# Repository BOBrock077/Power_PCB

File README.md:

# MAX1954 Buck Converter Practice

Personal power supply design practice using MAX1954 synchronous buck controller.

Main goals:
- Practice synchronous buck converter design
- Learn power stage PCB layout
- Evaluate DH/LX switching behavior
- Test snubber effectiveness
- Observe switching noise and ringing

---

## Current Status

- [x] Schematic
- [ ] PCB layout
- [ ] ERC/DRC cleanup
- [ ] Prototype
- [ ] Oscilloscope validation

---

## Basic Specs

| Item | Value |
|---|---|
| VIN | 12V |
| VOUT | TBD |
| Controller | MAX1954 |
| MOSFET | FDS6690A |
| Topology | Synchronous Buck |

---

## Things To Learn

- Bootstrap circuit behavior
- DH/LX waveform
- MOSFET switching loss
- Snubber tuning
- Ground return path
- Switching loop minimization

---

## Notes

### Snubber

Current value:
- 1500pF capacitor
- resistor TBD

Need waveform validation later.

---

## TODO

- [ ] Add input bulk capacitor
- [ ] Check compensation network
- [ ] Measure LX ringing
- [ ] Optimize MOSFET placement
- [ ] Thermal estimation

---

## Git Commit Style

```bash
PCB: move MOSFET closer to controller
SCH: update bootstrap capacitor
TEST: measure LX overshoot
```

---

## References

- MAX1954 Datasheet
- TI Power Layout Guidelines
- Analog Devices Buck Converter Layout Notes

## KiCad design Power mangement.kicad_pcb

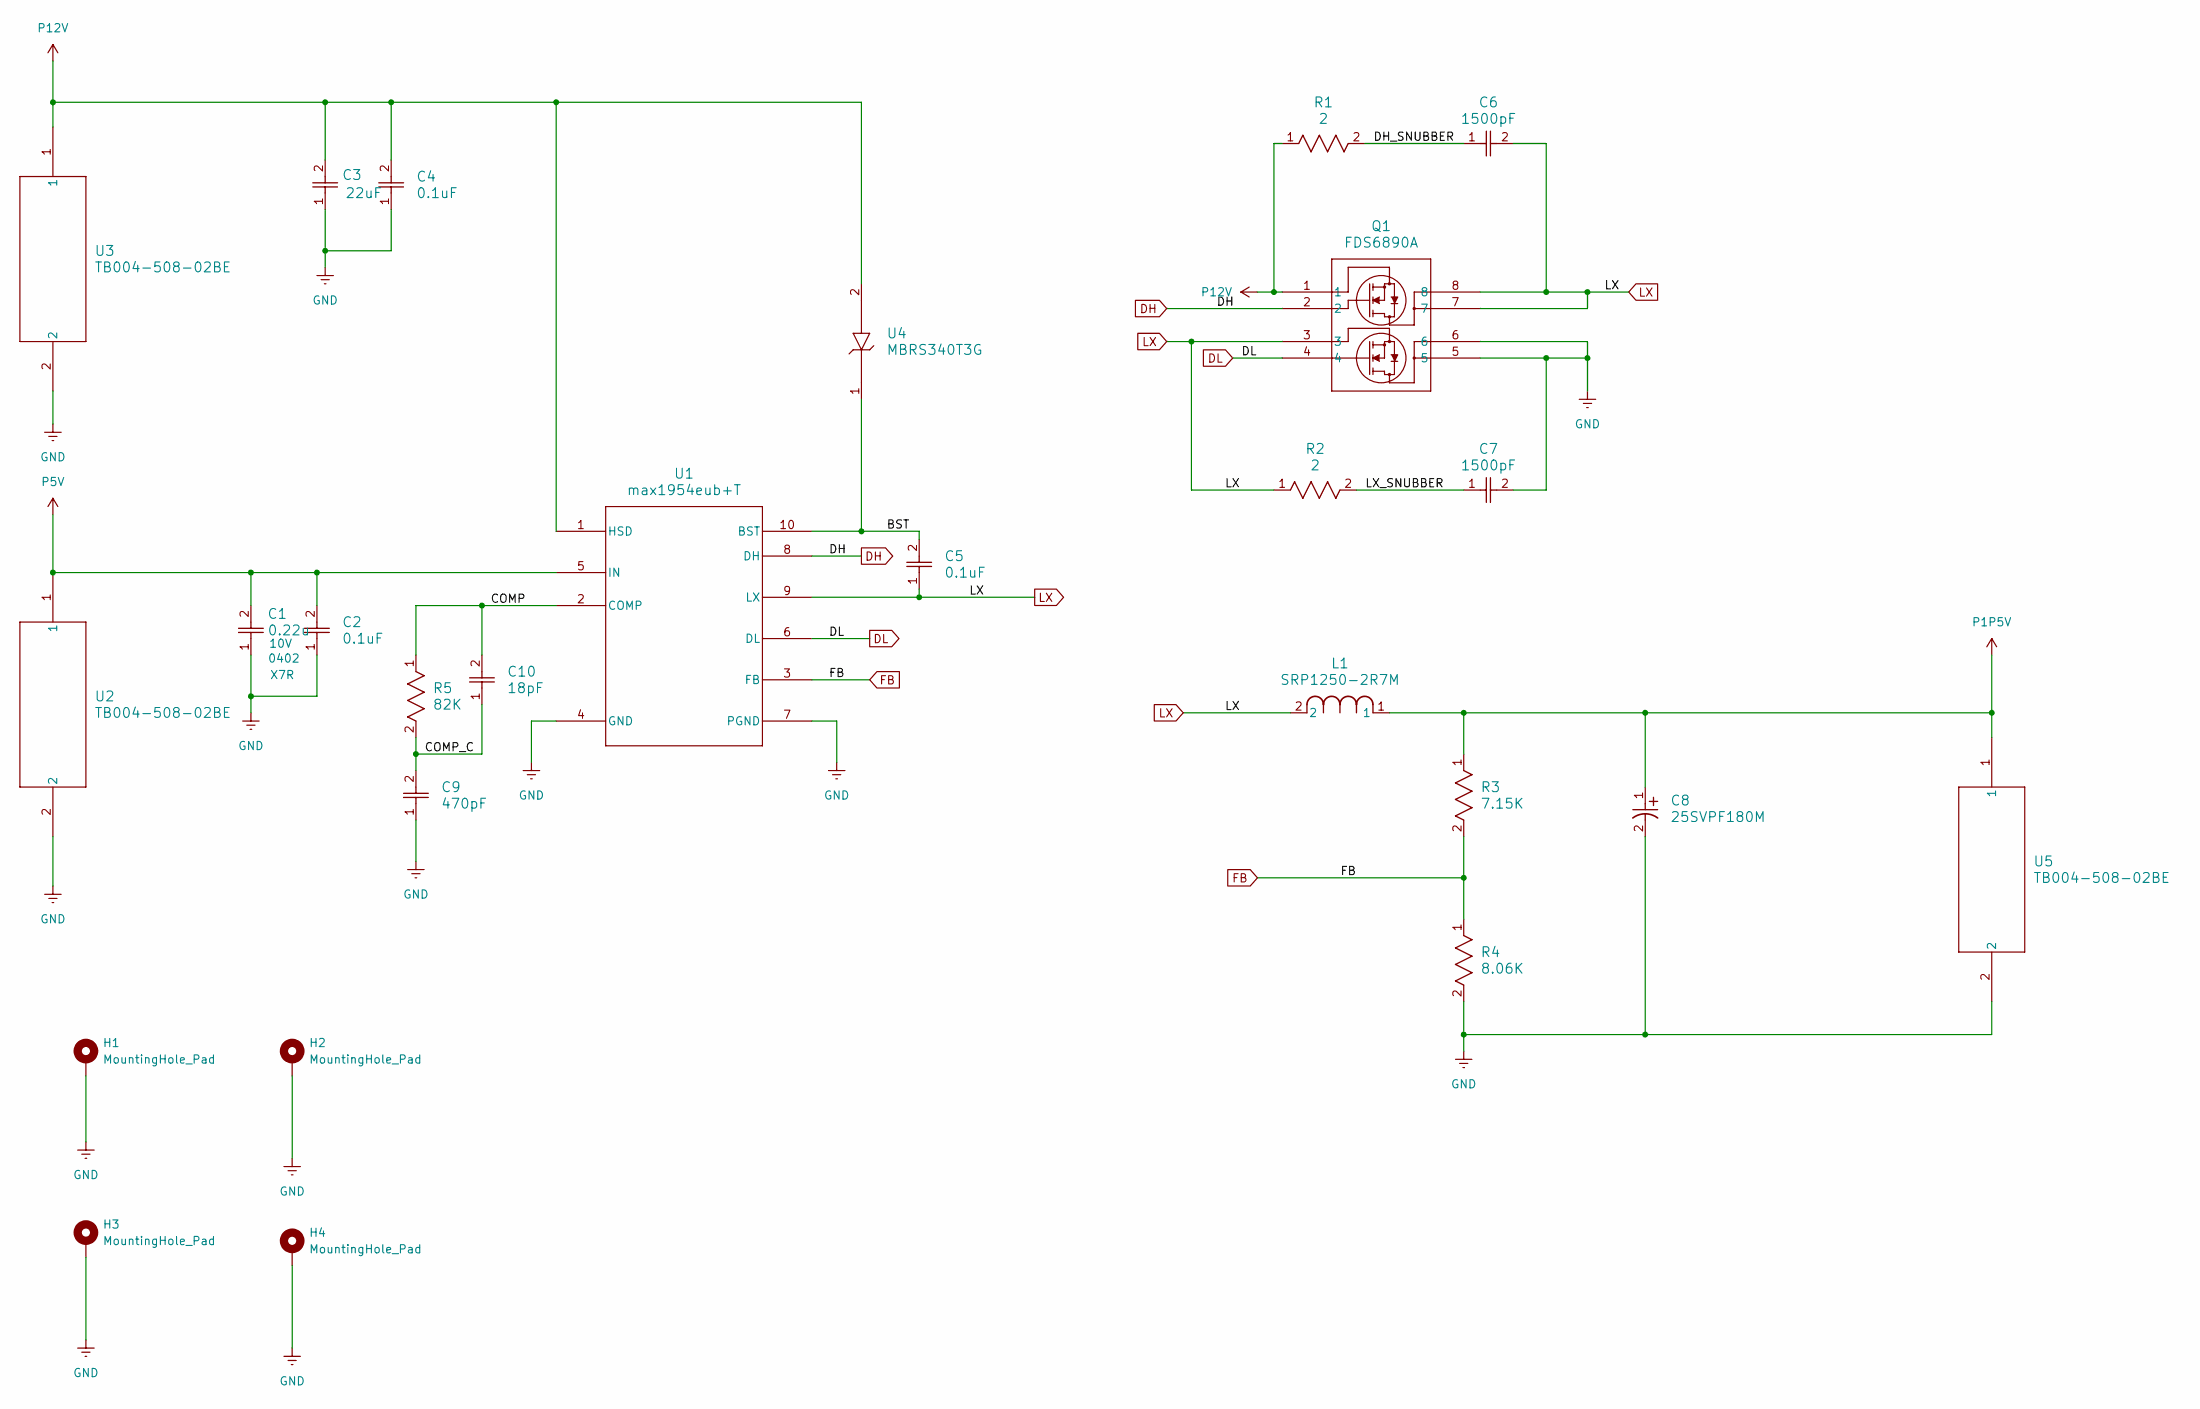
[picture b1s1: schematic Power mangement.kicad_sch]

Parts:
C1: 0.22u; CAP_1005_TDK; MPN CGA2B1X7R1A224M050BC
C2: 0.1uF; CAP_GRM155Z_MUR
C3: 22uF; G-21_MUR
C4, C5: 0.1uF; 0402_AVX
C6, C7: 1500pF; CAP_0805J_AVX
C8: 25SVPF180M; PCAP_SVP_E12_PAN
C9: 470pF; CAP_0402_N_WAL
C10: 18pF; CAP_0603G_AVX
H1, H2, H3, H4: MountingHole_Pad; MountingHole_3.2mm_M3_Pad
L1: SRP1250-2R7M; IND_BOURNS_SRP1250
Q1: FDS6890A; SOIC-8_FS_PKG_Code_S1_OSI
R1, R2: 2; RC0805N_VIS
R3: 7.15K; RES0402_CPF_TYCO_TYC
R4: 8.06K; RES0402_RN73_TYCO_TYC
R5: 82K; RES0402_CRG_TYCO_TYC
U1: max1954eub+T; 21-0061L_MXM
U2, U3, U5: TB004-508-02BE; TB004-508-02BE_CUD
U4: MBRS340T3G; SMC_ONS

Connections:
/BST: C5.2, U1.10 (BST), U4.1
/COMP: C10.2, R5.1, U1.2 (COMP)
/COMP_C: C9.2, C10.1, R5.2
/DH_SNUBBER: C6.1, R1.2
/LX_SNUBBER: C7.1, R2.2
DH: Q1.2, U1.8 (DH)
DL: Q1.4, U1.6 (DL)
FB: R3.2, R4.1, U1.3 (FB)
GND: C1.1, C2.1, C3.1, C4.1, C7.2, C8.2, C9.1, H1.1 (1_1), H2.1 (1_1), H3.1 (1_1), H4.1 (1_1), Q1.5, Q1.6, R4.2, U1.4 (GND), U1.7 (PGND), U2.2, U3.2, U5.2; also elsewhere on the board
LX: C5.1, C6.2, L1.2, Q1.3, Q1.7, Q1.8, R2.1, U1.9 (LX)
P1P5V: C8.1, L1.1, R3.1, U5.1
P5V: C1.2, C2.2, U1.5 (IN), U2.1
P12V: C3.2, C4.2, Q1.1, R1.1, U1.1 (HSD), U3.1, U4.2; also elsewhere on the board

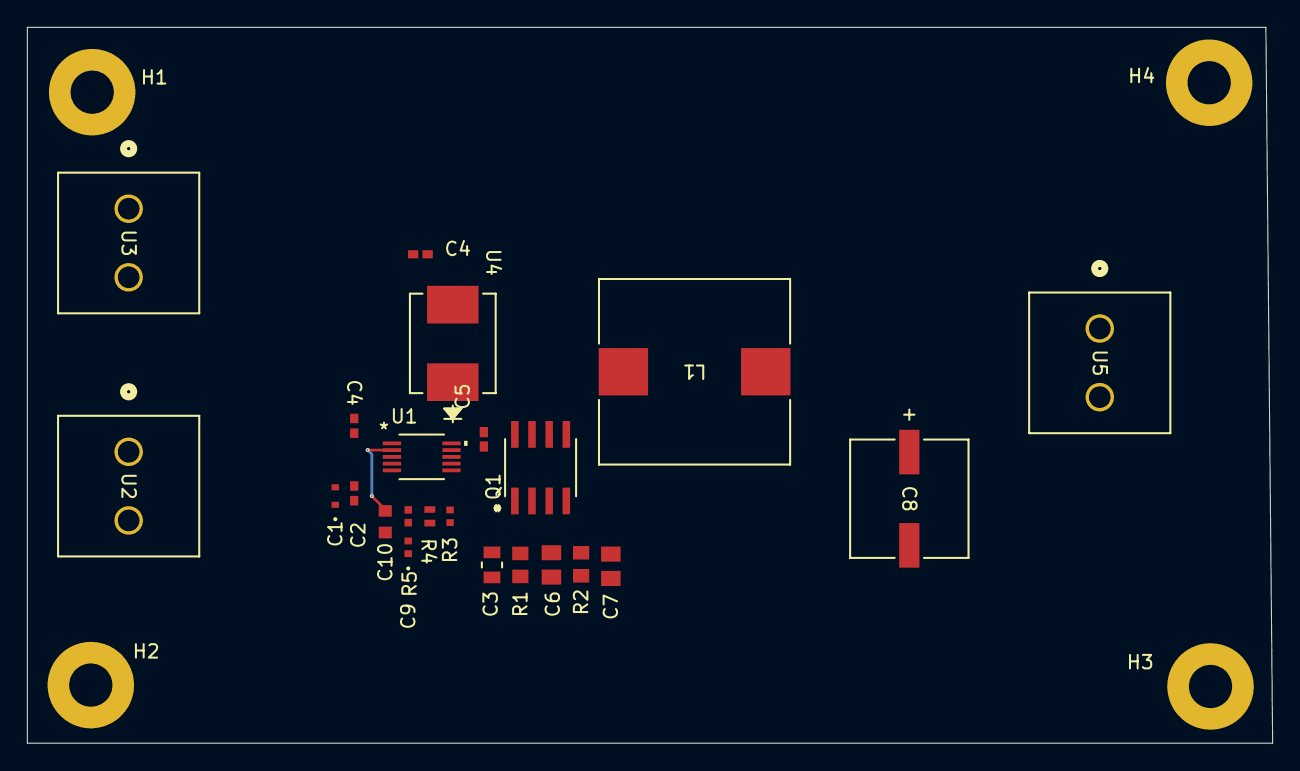
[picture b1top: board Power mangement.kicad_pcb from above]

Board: 4 copper layers, 92.2 x 53.0 mm, 27 parts (0 on the bottom side), 13 nets.

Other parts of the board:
C4#2: 0.1uF; CAP_GRM155Z_MUR

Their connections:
GND: C4#2.1; also elsewhere on the board
P12V: C4#2.2; also elsewhere on the board

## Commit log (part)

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2026-05-17 PCB layout change placement
2026-05-17 Initialize README.md for MAX1954 buck converter project
    Added detailed project information for MAX1954 buck converter design, including goals, current status, specifications, learning objectives, notes, and references.
